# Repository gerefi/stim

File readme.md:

[Interactive Pinout](https://gerefi.com/docs/pinouts/stim/)

See https://github.com/gerefi/gerefi-hardware/tree/main/digital-inputs for firmware

Part of https://github.com/gerefi/gerefi infrastucture

https://github.com/gerefi/gerefi/wiki/dev-hardware-quality-control

# Changelog

## rev 0.2

* CAN bus
* superseal header

##  rev 0.1
* it works!

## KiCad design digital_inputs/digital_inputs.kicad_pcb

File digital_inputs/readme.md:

# Digital Inputs
- 48 channels of high/low digital inputs
- pin requirment: 4 ADC inputs and 9 GPIO

GPIO:
* output: x4 address pins
* output: x4 test control pins
* output: mux off

See https://github.com/gerefi/stim/issues/6

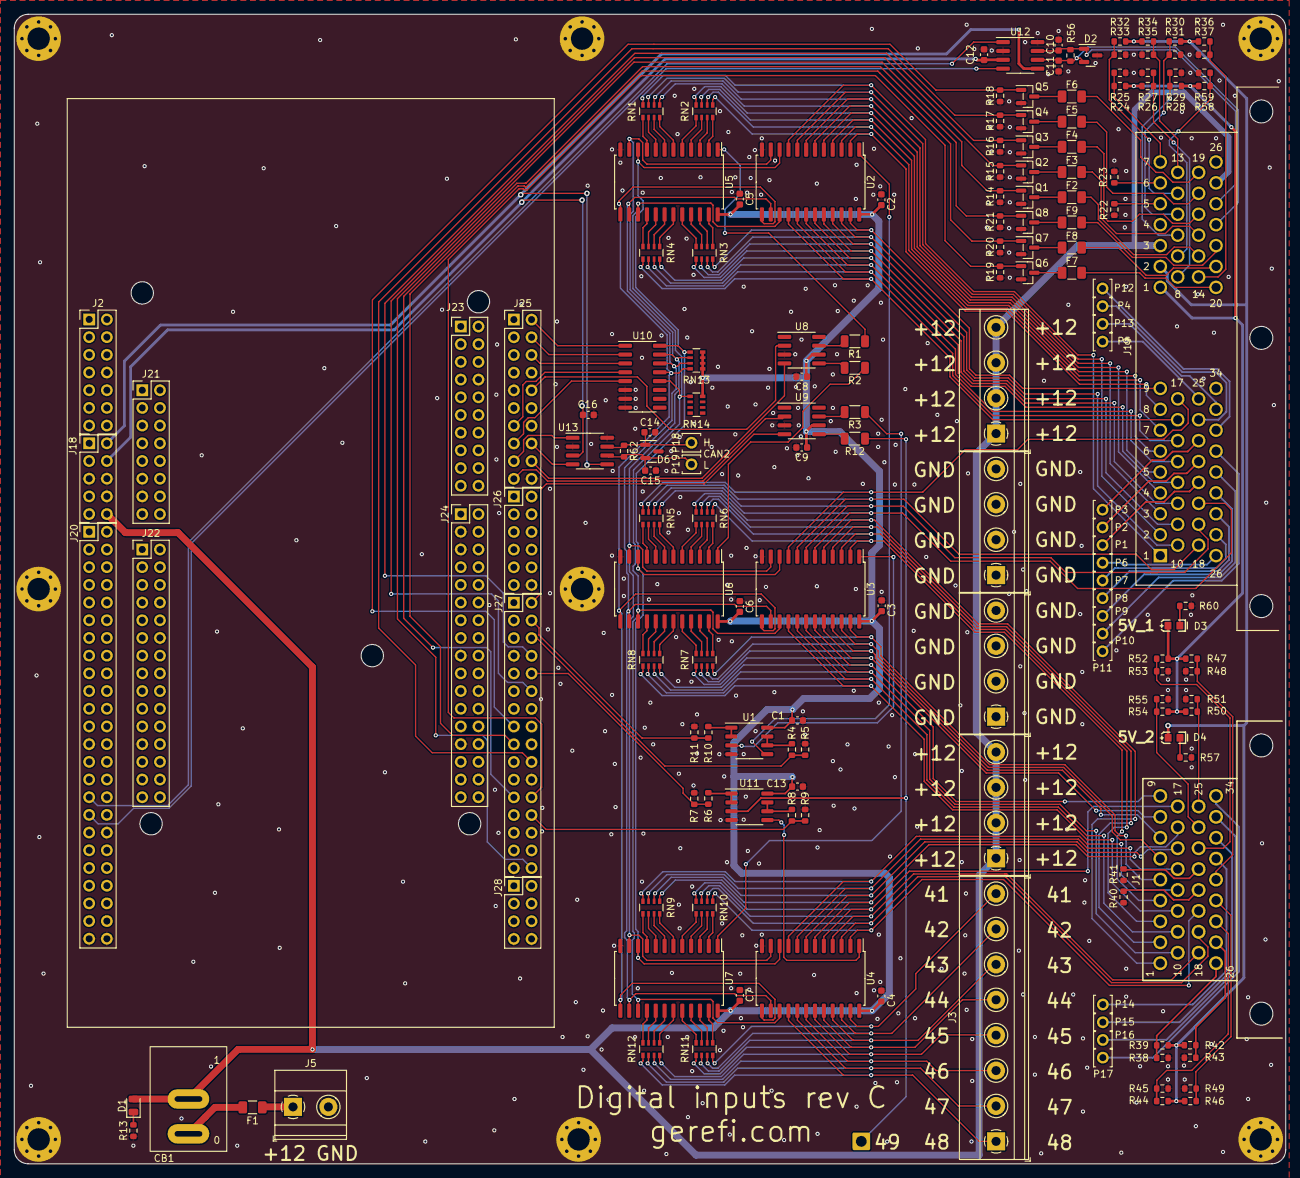
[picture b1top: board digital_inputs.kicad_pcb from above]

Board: 2 copper layers, 182.5 x 165.0 mm, 179 parts (0 on the bottom side), 209 nets.

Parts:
C1, C2, C3, C4, C5, C6, C7, C8, C9, C12, C13, C16: 100n; C_0603_1608Metric
C10, C11, C14, C15: 47p; C_0603_1608Metric
CB1: CircuitBreaker_1P; RS601HL-1010011BB
D1: LED; LED_0805_2012Metric
D2, D6: PESD1CAN; SOT-23
D3, D4: LED-RED-0603; LED-0603
F1: 1.8A; Fuse_1206_3216Metric
F2, F3, F4, F5, F6, F7, F8, F9: nSMD005; Fuse_1206_3216Metric
H1, H2, H3, H4, H5: MountingHole; MountingHole_3.2mm_M3
J1: 6437288-2
J2: Conn_02x07_Odd_Even; PinHeader_2x07_P2.54mm_Vertical
J3: Conn_01x08; TerminalBlock_Phoenix_MKDS-1,5-8-5.08_1x08_P5.08mm_Horizont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
J4: Conn_01x01; SolderWire-0.75sqmm_1x01_D1.25mm_OD2.3mm
J5: Conn_01x02; TerminalBlock_Phoenix_MKDS-1,5-2-5.08_1x02_P5.08mm_Horizont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
J6, J7, J8, J9: Conn_01x04; TerminalBlock_Phoenix_MKDS-1,5-4-5.08_1x04_P5.08mm_Horizont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
J10, J11, J12, J13, J14, J15, J16, J17: Conn_01x01; MountingHole_3.2mm_M3_Pad_Via
J18: Conn_02x05_Odd_Even; PinHeader_2x05_P2.54mm_Vertical
J19: 6437288-3; TE_6437288-3
J20: Conn_02x24_Odd_Even; PinHeader_2x24_P2.54mm_Vertical
J21: Conn_02x08_Odd_Even; PinHeader_2x08_P2.54mm_Vertical
J22: Conn_02x15_Odd_Even; PinHeader_2x15_P2.54mm_Vertical
J23, J25: Conn_02x10_Odd_Even; PinHeader_2x10_P2.54mm_Vertical
J24: Conn_02x17_Odd_Even; PinHeader_2x17_P2.54mm_Vertical
J26: Conn_02x06_Odd_Even; PinHeader_2x06_P2.54mm_Vertical
J27: Conn_02x16_Odd_Even; PinHeader_2x16_P2.54mm_Vertical
J28: Conn_02x04_Odd_Even; PinHeader_2x04_P2.54mm_Vertical
P1, P2, P3, P4, P5, P6, P7, P8, P9, P10, P11, P12, P13, P14, P15, P16, P17, P18, P19: Pad; PAD-TH
Q1, Q2, Q3, Q4, Q5, Q6, Q7, Q8: AO3400A; SOT-23
R1, R2, R3, R12: 1.2k; R_1206_3216Metric
R4, R6, R8, R10, R14, R15, R16, R17, R18, R19, R20, R21, R57, R60: 4.7k; R_0603_1608Metric
R5, R7, R9, R11: 1.5k; R_0603_1608Metric
R13: 13k; R_0603_1608Metric
R22, R40: 1k; R_0603_1608Metric
R23, R41: 2k; R_0603_1608Metric
R24, R26, R30, R32, R36, R39, R49: 820; R_0603_1608Metric
R25, R29, R44, R46, R47, R59: 100; R_0603_1608Metric
R27: 120; R_0603_1608Metric
R28, R34, R43, R51, R52, R54, R55: 470; R_0603_1608Metric
R31, R35, R42: 220; R_0603_1608Metric
R33, R45, R50, R53: 330; R_0603_1608Metric
R37, R38, R58: 510; R_0603_1608Metric
R48: 910; R_0603_1608Metric
R56, R62: DNP; R_0603_1608Metric
RN1, RN2, RN3, RN4, RN5, RN6, RN7, RN8, RN9, RN10, RN11, RN12: 0; R_Array_Convex_4x0603
RN13, RN14: 10k; R_Array_Convex_4x0603
U1, U11: OPA2192IDR; SO-8_3.9x4.9mm_P1.27mm
U2, U3, U4, U5, U6, U7: CD4067BM96; SOIC-24W_7.5x15.4mm_P1.27mm
U8, U9: TC4427; SOIC-8_3.9x4.9mm_P1.27mm
U10: ULN2003A; SOIC-16_3.9x9.9mm_P1.27mm
U12, U13: TJA1051T-3; SOIC-8_3.9x4.9mm_P1.27mm

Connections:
+3.3V: J18.2 (+3V3), U12.5 (VIO), U13.5 (VIO)
+5V: C12.2, C16.2, J18.4 (+5V), U12.3 (VCC), U13.3 (VCC)
+12V: C1.2, C2.2, C3.2, C4.2, C5.2, C6.2, C7.2, C8.1, C9.1, C13.2, CB1.2, D1.2 (A), J8.1, J8.2, J8.3, J8.4, J9.1, J9.2, J9.3, J9.4, J18.10 (VIN), J19.37 (3B), J19.59 (25B), RN13.1 (R1.1), RN13.2 (R2.1), RN13.3 (R3.1), RN13.4 (R4.1), RN14.4 (R4.1), U1.8 (V+), U2.24 (VDD), U3.24 (VDD), U4.24 (VDD), U5.24 (VDD), U6.24 (VDD), U7.24 (VDD), U8.6 (VDD), U9.6 (VDD), U11.8 (V+)
/5V_1: D3.1 (A), J19.35 (1B), R24.1, R26.1, R28.1, R47.1, R50.1, R52.1, R54.1, R58.1
/5V_2: D4.1 (A), J19.36 (2B), R30.1, R32.1, R34.1, R36.1, R39.1, R42.1, R44.1, R46.1
/A0: RN13.5 (R4.2), U2.10 (A), U3.10 (A), U4.10 (A), U5.10 (A), U6.10 (A), U7.10 (A), U10.16 (O1)
/A1: RN13.6 (R3.2), U2.11 (B), U3.11 (B), U4.11 (B), U5.11 (B), U6.11 (B), U7.11 (B), U10.15 (O2)
/A2: RN13.7 (R2.2), U2.14 (C), U3.14 (C), U4.14 (C), U5.14 (C), U6.14 (C), U7.14 (C), U10.14 (O3)
/A3: RN13.8 (R1.2), U2.13 (D), U3.13 (D), U4.13 (D), U5.13 (D), U6.13 (D), U7.13 (D), U10.13 (O4)
/ADR0: J25.2 (PC8), U10.1 (I1)
/ADR1: J25.4 (PC6), U10.2 (I2)
/ADR2: J25.6 (PC5), U10.3 (I3)
/ADR3: J25.13 (PA6), U10.4 (I4)
/CAN2_H: C14.1, D6.1 (G), P18.1, R62.1, U13.7 (CANH)
/CAN2_L: C15.2, D6.2 (D), P19.1, R62.2, U13.6 (CANL)
/CAN2_RX: J25.16 (PB12), U13.4 (RXD)
/CAN2_TX: J25.17 (PB6), U13.1 (TXD)
/CAN_H: C10.1, D2.1 (G), J19.58 (24B), R56.1, U12.7 (CANH)
/CAN_L: C11.2, D2.2 (D), J19.57 (23B), R56.2, U12.6 (CANL)
/CAN_RX: J20.33 (PD0), U12.4 (RXD)
/CAN_TX: J20.31 (PD1), U12.1 (TXD)
/DIG_0: J27.32 (PE0), Q1.1 (G), R14.2
/DIG_1: J27.12 (PE7), Q2.1 (G), R15.2
/DIG_2: J27.8 (PE8), Q3.1 (G), R16.2
/DIG_3: J27.20 (PE9), Q4.1 (G), R17.2
/DIG_4: J27.15 (PE10), Q5.1 (G), R18.2
/DIG_5: J27.24 (PE11), Q6.1 (G), R19.2
/DIG_6: J27.17 (PE12), Q7.1 (G), R20.2
/DIG_7: J27.23 (PE13), Q8.1 (G), R21.2
/IN0: J27.6 (PF4), R4.1, R5.2
/IN1: J27.4 (PF5), R10.1, R11.2
/IN2: J27.26 (PF3), R8.1, R9.2
/IN3: J27.10 (PF10), R6.1, R7.2
/MUX_OFF: J25.15 (PA7), U10.5 (I5)
/OFF: RN14.5 (R4.2), U2.15 (INH), U3.15 (INH), U4.15 (INH), U5.15 (INH), U6.15 (INH), U7.15 (INH), U10.12 (O5)
/OUT0: J25.10 (PD8), U8.2 (IN_A)
/OUT1: J25.18 (PB11), U8.4 (IN_B)
/OUT2: J25.19 (PC7), U9.2 (IN_A)
/OUT3: J27.2 (PC4), U9.4 (IN_B)
/OUT_DIG_0: F2.2, J19.49 (15B)
/OUT_DIG_1: F3.2, J19.50 (16B)
/OUT_DIG_2: F4.2, J19.51 (17B)
/OUT_DIG_3: F5.2, J19.52 (18B)
/OUT_DIG_4: F6.2, J19.53 (19B)
/OUT_DIG_5: F7.2, J19.54 (20B)
/OUT_DIG_6: F8.2, J19.55 (21B)
/OUT_DIG_7: F9.2, J19.56 (22B)
/REF1: J19.41 (7B), R24.2, R25.1
/REF2: J19.42 (8B), R26.2, R27.1
/REF3: J19.43 (9B), R58.2, R59.1
/REF4: J19.44 (10B), R28.2, R29.1
/REF5: J19.45 (11B), R30.2, R31.1
/REF6: J19.46 (12B), R32.2, R33.1
/REF7: J19.47 (13B), R34.2, R35.1
/REF8: J19.48 (14B), R36.2, R37.1
/REF9: J1.23 (23A), R52.2, R53.1
/REF10: J1.24 (24A), R54.2, R55.1
/REF11: J1.25 (25A), R50.2, R51.1
/REF12: J1.26 (26A), R38.2, R39.2
/REF13: J1.27 (27A), R42.2, R43.1
/REF14: J1.28 (28A), R44.2, R45.1
/REF15: J1.29 (29A), R46.2, R49.1
/REF16: J1.30 (30A), R47.2, R48.1
/TST1: J19.1 (1A), RN1.8 (R1.2), U2.9 (X0)
/TST2: J19.2 (2A), RN1.7 (R2.2), U2.8 (X1)
/TST3: J19.3 (3A), RN1.6 (R3.2), U2.7 (X2)
/TST4: J19.4 (4A), RN1.5 (R4.2), U2.6 (X3)
/TST5: J19.5 (5A), RN2.8 (R1.2), U2.5 (X4)
/TST6: J19.6 (6A), RN2.7 (R2.2), U2.4 (X5)
/TST7: J19.7 (7A), RN2.6 (R3.2), U2.3 (X6)
/TST8: J19.8 (8A), RN2.5 (R4.2), U2.2 (X7)
/TST9: J19.9 (9A), RN3.8 (R1.2), U2.23 (X8)
/TST10: J19.10 (10A), RN3.7 (R2.2), U2.22 (X9)
/TST11: J19.11 (11A), RN3.6 (R3.2), U2.21 (X10)
/TST12: J19.12 (12A), RN3.5 (R4.2), U2.20 (X11)
/TST13: J19.13 (13A), RN4.8 (R1.2), U2.19 (X12)
/TST14: J19.14 (14A), RN4.7 (R2.2), U2.18 (X13)
/TST15: J19.15 (15A), RN4.6 (R3.2), U2.17 (X14)
/TST16: J19.16 (16A), RN4.5 (R4.2), U2.16 (X15)
/TST17: J19.17 (17A), RN5.4 (R4.1), U3.9 (X0)
/TST18: J19.18 (18A), RN5.3 (R3.1), U3.8 (X1)
/TST19: J19.19 (19A), RN5.2 (R2.1), U3.7 (X2)
/TST20: J19.20 (20A), RN5.1 (R1.1), U3.6 (X3)
/TST21: J1.1 (1A), RN6.4 (R4.1), U3.5 (X4)
/TST22: J1.2 (2A), RN6.3 (R3.1), U3.4 (X5)
/TST23: J1.3 (3A), RN6.2 (R2.1), U3.3 (X6)
/TST24: J1.4 (4A), RN6.1 (R1.1), U3.2 (X7)
/TST25: J1.5 (5A), RN7.4 (R4.1), U3.23 (X8)
/TST26: J1.6 (6A), RN7.3 (R3.1), U3.22 (X9)
/TST27: J1.7 (7A), RN7.2 (R2.1), U3.21 (X10)
/TST28: J1.8 (8A), RN7.1 (R1.1), U3.20 (X11)
/TST29: J1.9 (9A), RN8.4 (R4.1), U3.19 (X12)
/TST30: J1.10 (10A), RN8.3 (R3.1), U3.18 (X13)
/TST31: J1.11 (11A), RN8.2 (R2.1), U3.17 (X14)
/TST32: J1.12 (12A), RN8.1 (R1.1), U3.16 (X15)
/TST33: J1.13 (13A), RN9.4 (R4.1), U4.9 (X0)
/TST34: J1.14 (14A), RN9.3 (R3.1), U4.8 (X1)
/TST35: J1.15 (15A), RN9.2 (R2.1), U4.7 (X2)
/TST36: J1.16 (16A), RN9.1 (R1.1), U4.6 (X3)
/TST37: J1.17 (17A), RN10.4 (R4.1), U4.5 (X4)
/TST38: J1.18 (18A), RN10.3 (R3.1), U4.4 (X5)
/TST39: J1.19 (19A), RN10.2 (R2.1), U4.3 (X6)
/TST40: J1.20 (20A), RN10.1 (R1.1), U4.2 (X7)
/TST41: J3.8, RN11.4 (R4.1), U4.23 (X8)
/TST42: J3.7, RN11.3 (R3.1), U4.22 (X9)
/TST43: J3.6, RN11.2 (R2.1), U4.21 (X10)
/TST44: J3.5, RN11.1 (R1.1), U4.20 (X11)
/TST45: J3.4, RN12.4 (R4.1), U4.19 (X12)
/TST46: J3.3, RN12.3 (R3.1), U4.18 (X13)
/TST47: J3.2, RN12.2 (R2.1), U4.17 (X14)
/TST48: J3.1, RN12.1 (R1.1), U4.16 (X15)
/TST49: J4.1, R12.1, U11.3 (+)
GND: C1.1, C2.1, C3.1, C4.1, C5.1, C6.1, C7.1, C8.2, C9.2, C10.2, C11.1, C12.1, C13.1, C14.2, C15.1, C16.1, D2.3 (S), D6.3 (S), J2.8 (GND), J5.2, J6.1, J6.2, J6.3, J6.4, J7.1, J7.2, J7.3, J7.4, J10.1, J11.1, J12.1, J13.1, J14.1, J15.1, J16.1, J17.1, J18.5 (GND), J18.6 (GND), J18.8 (GND), J19.34 (34A), J19.38 (4B), J19.60 (26B), J20.25 (GND), J20.36 (GND), J20.47 (GND), J20.48 (GND), J21.11 (GND), J21.13 (GND), J22.12 (GND), J22.23 (GND), J23.8 (GND), J24.3 (AGND_CN10), J24.5 (GND), J24.17 (GND), J24.22 (GND), J24.27 (GND), J25.9 (GND), J25.20 (GND), J26.12 (AGND), J27.7 (GND), J27.22 (GND), J27.31 (GND), J28.7 (GND), J28.8 (GND), Q1.3 (S), Q2.3 (S), Q3.3 (S), Q4.3 (S), Q5.3 (S), Q6.3 (S), Q7.3 (S), Q8.3 (S), R5.1, R7.1, R9.1, R11.1, R13.1, R14.1, R15.1, R16.1, R17.1, R18.1, R19.1, R20.1, R21.1, R22.1, R23.1, R25.2, R27.2, R29.2, R31.2, R33.2, R35.2, R37.2, R38.1, R40.1, R41.1, R43.2, R45.2, R48.2, R49.2, R51.2, R53.2, R55.2, R57.1, R59.2, R60.1, U1.4 (V-), U2.12 (VSS), U3.12 (VSS), U4.12 (VSS), U5.12 (VSS), U6.12 (VSS), U7.12 (VSS), U8.3 (GND), U9.3 (GND), U10.6 (I6), U10.7 (I7), U10.8 (GND), U11.4 (V-), U12.2 (GND), U12.8 (S), U13.2 (GND), U13.8 (S)
unnamed: CB1.1, F1.1
unnamed: D1.1 (K), R13.2
unnamed: D3.2 (K), R60.2
unnamed: D4.2 (K), R57.2
unnamed: J1.21 (21A), R40.2
unnamed: J1.22 (22A), R41.2
unnamed: J1.31 (31A), P14.1
unnamed: J1.32 (32A), P15.1
unnamed: J1.33 (33A), P16.1
unnamed: J1.34 (34A), P17.1
unnamed: F1.2, J5.1
unnamed: J19.21 (21A), P1.1
unnamed: J19.22 (22A), P2.1
unnamed: J19.23 (23A), P3.1
unnamed: J19.24 (24A), P4.1
unnamed: J19.25 (25A), P5.1
unnamed: J19.26 (26A), P6.1
unnamed: J19.27 (27A), P7.1
unnamed: J19.28 (28A), P8.1
unnamed: J19.29 (29A), P9.1
unnamed: J19.30 (30A), P10.1
unnamed: J19.31 (31A), P11.1
unnamed: J19.32 (32A), P12.1
unnamed: J19.33 (33A), P13.1
unnamed: J19.39 (5B), R22.2
unnamed: J19.40 (6B), R23.2
unnamed: F2.1, Q1.2 (D)
unnamed: F3.1, Q2.2 (D)
unnamed: F4.1, Q3.2 (D)
unnamed: F5.1, Q4.2 (D)
unnamed: F6.1, Q5.2 (D)
unnamed: F7.1, Q6.2 (D)
unnamed: F8.1, Q7.2 (D)
unnamed: F9.1, Q8.2 (D)
unnamed: RN1.1 (R1.1), U5.9 (X0)
unnamed: RN1.2 (R2.1), U5.8 (X1)
unnamed: RN1.3 (R3.1), U5.7 (X2)
unnamed: RN1.4 (R4.1), U5.6 (X3)
unnamed: RN2.1 (R1.1), U5.5 (X4)
unnamed: RN2.2 (R2.1), U5.4 (X5)
unnamed: RN2.3 (R3.1), U5.3 (X6)
unnamed: RN2.4 (R4.1), U5.2 (X7)
unnamed: RN3.1 (R1.1), U5.23 (X8)
unnamed: RN3.2 (R2.1), U5.22 (X9)
unnamed: RN3.3 (R3.1), U5.21 (X10)
unnamed: RN3.4 (R4.1), U5.20 (X11)
unnamed: RN4.1 (R1.1), U5.19 (X12)
unnamed: RN4.2 (R2.1), U5.18 (X13)
unnamed: RN4.3 (R3.1), U5.17 (X14)
unnamed: RN4.4 (R4.1), U5.16 (X15)
unnamed: RN5.8 (R1.2), U6.6 (X3)
unnamed: RN5.7 (R2.2), U6.7 (X2)
unnamed: RN5.6 (R3.2), U6.8 (X1)
unnamed: RN5.5 (R4.2), U6.9 (X0)
unnamed: RN6.8 (R1.2), U6.2 (X7)
unnamed: RN6.7 (R2.2), U6.3 (X6)
unnamed: RN6.6 (R3.2), U6.4 (X5)
unnamed: RN6.5 (R4.2), U6.5 (X4)
unnamed: RN7.8 (R1.2), U6.20 (X11)
unnamed: RN7.7 (R2.2), U6.21 (X10)
unnamed: RN7.6 (R3.2), U6.22 (X9)
unnamed: RN7.5 (R4.2), U6.23 (X8)
unnamed: RN8.8 (R1.2), U6.16 (X15)
unnamed: RN8.7 (R2.2), U6.17 (X14)
unnamed: RN8.6 (R3.2), U6.18 (X13)
unnamed: RN8.5 (R4.2), U6.19 (X12)
unnamed: RN9.8 (R1.2), U7.6 (X3)
unnamed: RN9.7 (R2.2), U7.7 (X2)
unnamed: RN9.6 (R3.2), U7.8 (X1)
unnamed: RN9.5 (R4.2), U7.9 (X0)
unnamed: RN10.8 (R1.2), U7.2 (X7)
unnamed: RN10.7 (R2.2), U7.3 (X6)
unnamed: RN10.6 (R3.2), U7.4 (X5)
unnamed: RN10.5 (R4.2), U7.5 (X4)
unnamed: RN11.8 (R1.2), U7.20 (X11)
unnamed: RN11.7 (R2.2), U7.21 (X10)
unnamed: RN11.6 (R3.2), U7.22 (X9)
unnamed: RN11.5 (R4.2), U7.23 (X8)
unnamed: RN12.8 (R1.2), U7.16 (X15)
unnamed: RN12.7 (R2.2), U7.17 (X14)
unnamed: RN12.6 (R3.2), U7.18 (X13)
unnamed: RN12.5 (R4.2), U7.19 (X12)
unnamed: U1.3 (+), U3.1 (X)
unnamed: R10.2, U1.1, U1.2 (-)
unnamed: U1.5 (+), U2.1 (X)
unnamed: R4.2, U1.6 (-), U1.7
unnamed: R1.1, U5.1 (X)
unnamed: R2.1, U6.1 (X)
unnamed: R3.1, U7.1 (X)
unnamed: R1.2, U8.7 (OUT_A)
unnamed: R2.2, U8.5 (OUT_B)
unnamed: R3.2, U9.7 (OUT_A)
unnamed: R12.2, U9.5 (OUT_B)
unnamed: R6.2, U11.1, U11.2 (-)
unnamed: U4.1 (X), U11.5 (+)
unnamed: R8.2, U11.6 (-), U11.7
